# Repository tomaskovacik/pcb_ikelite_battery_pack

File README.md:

# pcb_ikelite_battery_pack
PCB for ikelite 125/160/161 battery pack

3d printed case: https://www.thingiverse.com/thing:3521984

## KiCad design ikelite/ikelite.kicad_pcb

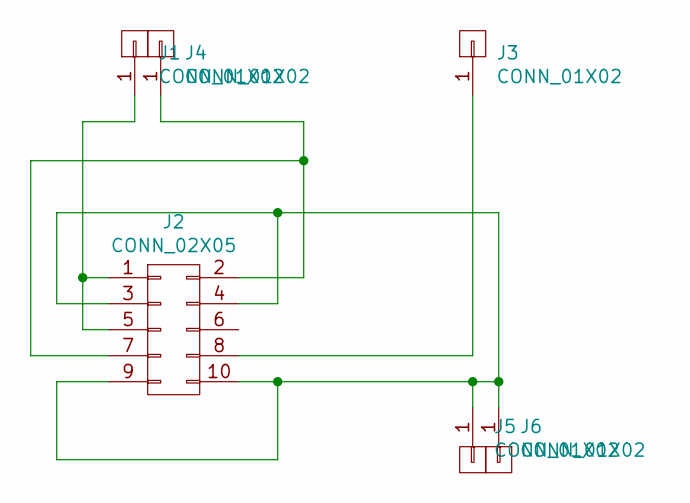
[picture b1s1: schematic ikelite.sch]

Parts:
J1, J3, J4, J5, J6: CONN_01X02; SolderWirePad_single_1-2mmDrill
J2: CONN_02X05; ikelite_switch

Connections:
unnamed: J1.1, J2.1, J2.5
unnamed: J2.2, J2.7, J4.1
unnamed: J2.8, J3.1
unnamed: J2.3, J2.4, J2.9, J2.10, J5.1, J6.1

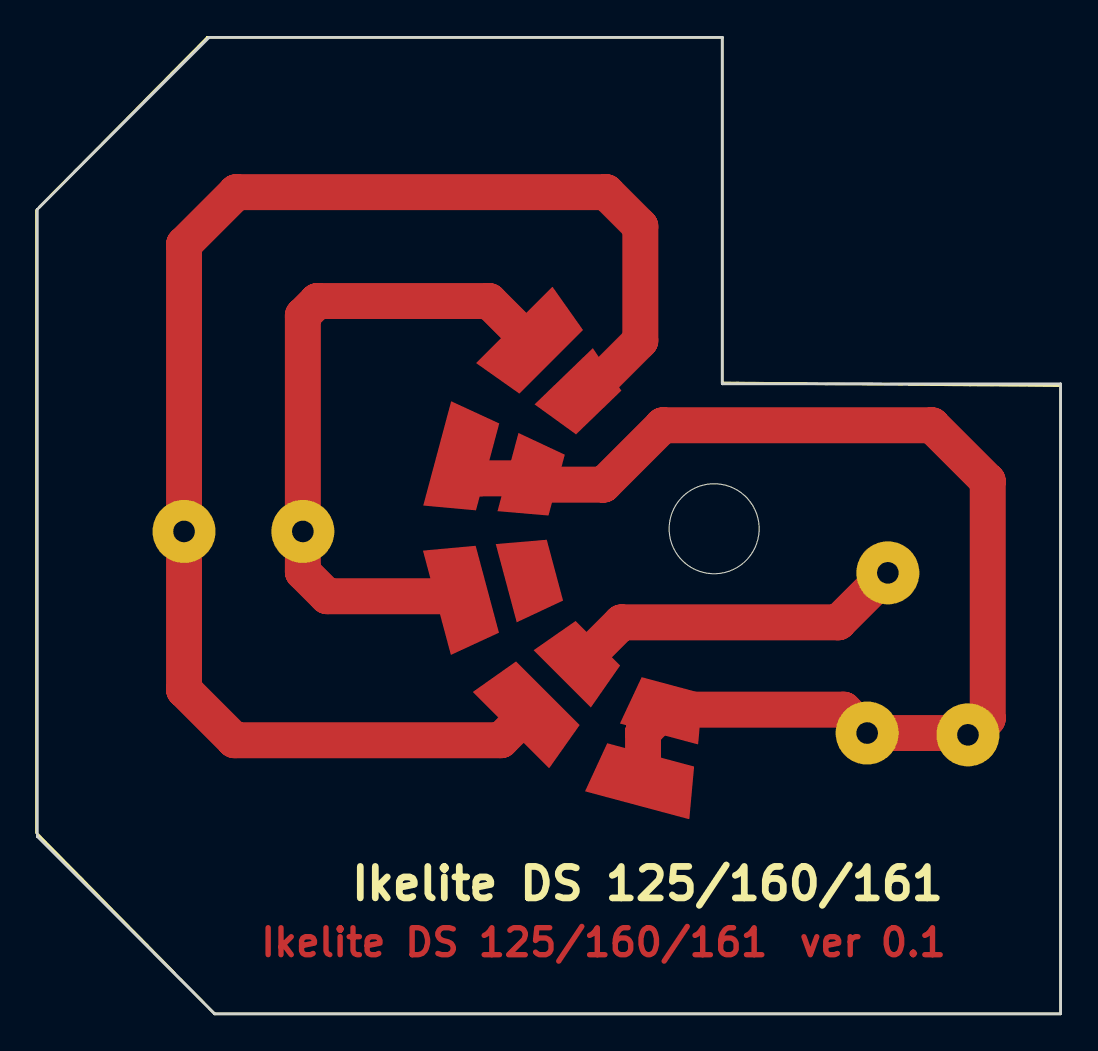
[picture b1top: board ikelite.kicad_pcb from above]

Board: 2 copper layers, 56.9 x 54.2 mm, 6 parts (0 on the bottom side), 4 nets.

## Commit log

2018-10-15 init
